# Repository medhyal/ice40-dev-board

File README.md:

# ice40-dev-board

ICE40 FPGA Development Board

- ICE40UP5K FPGA
- Built in Programmer

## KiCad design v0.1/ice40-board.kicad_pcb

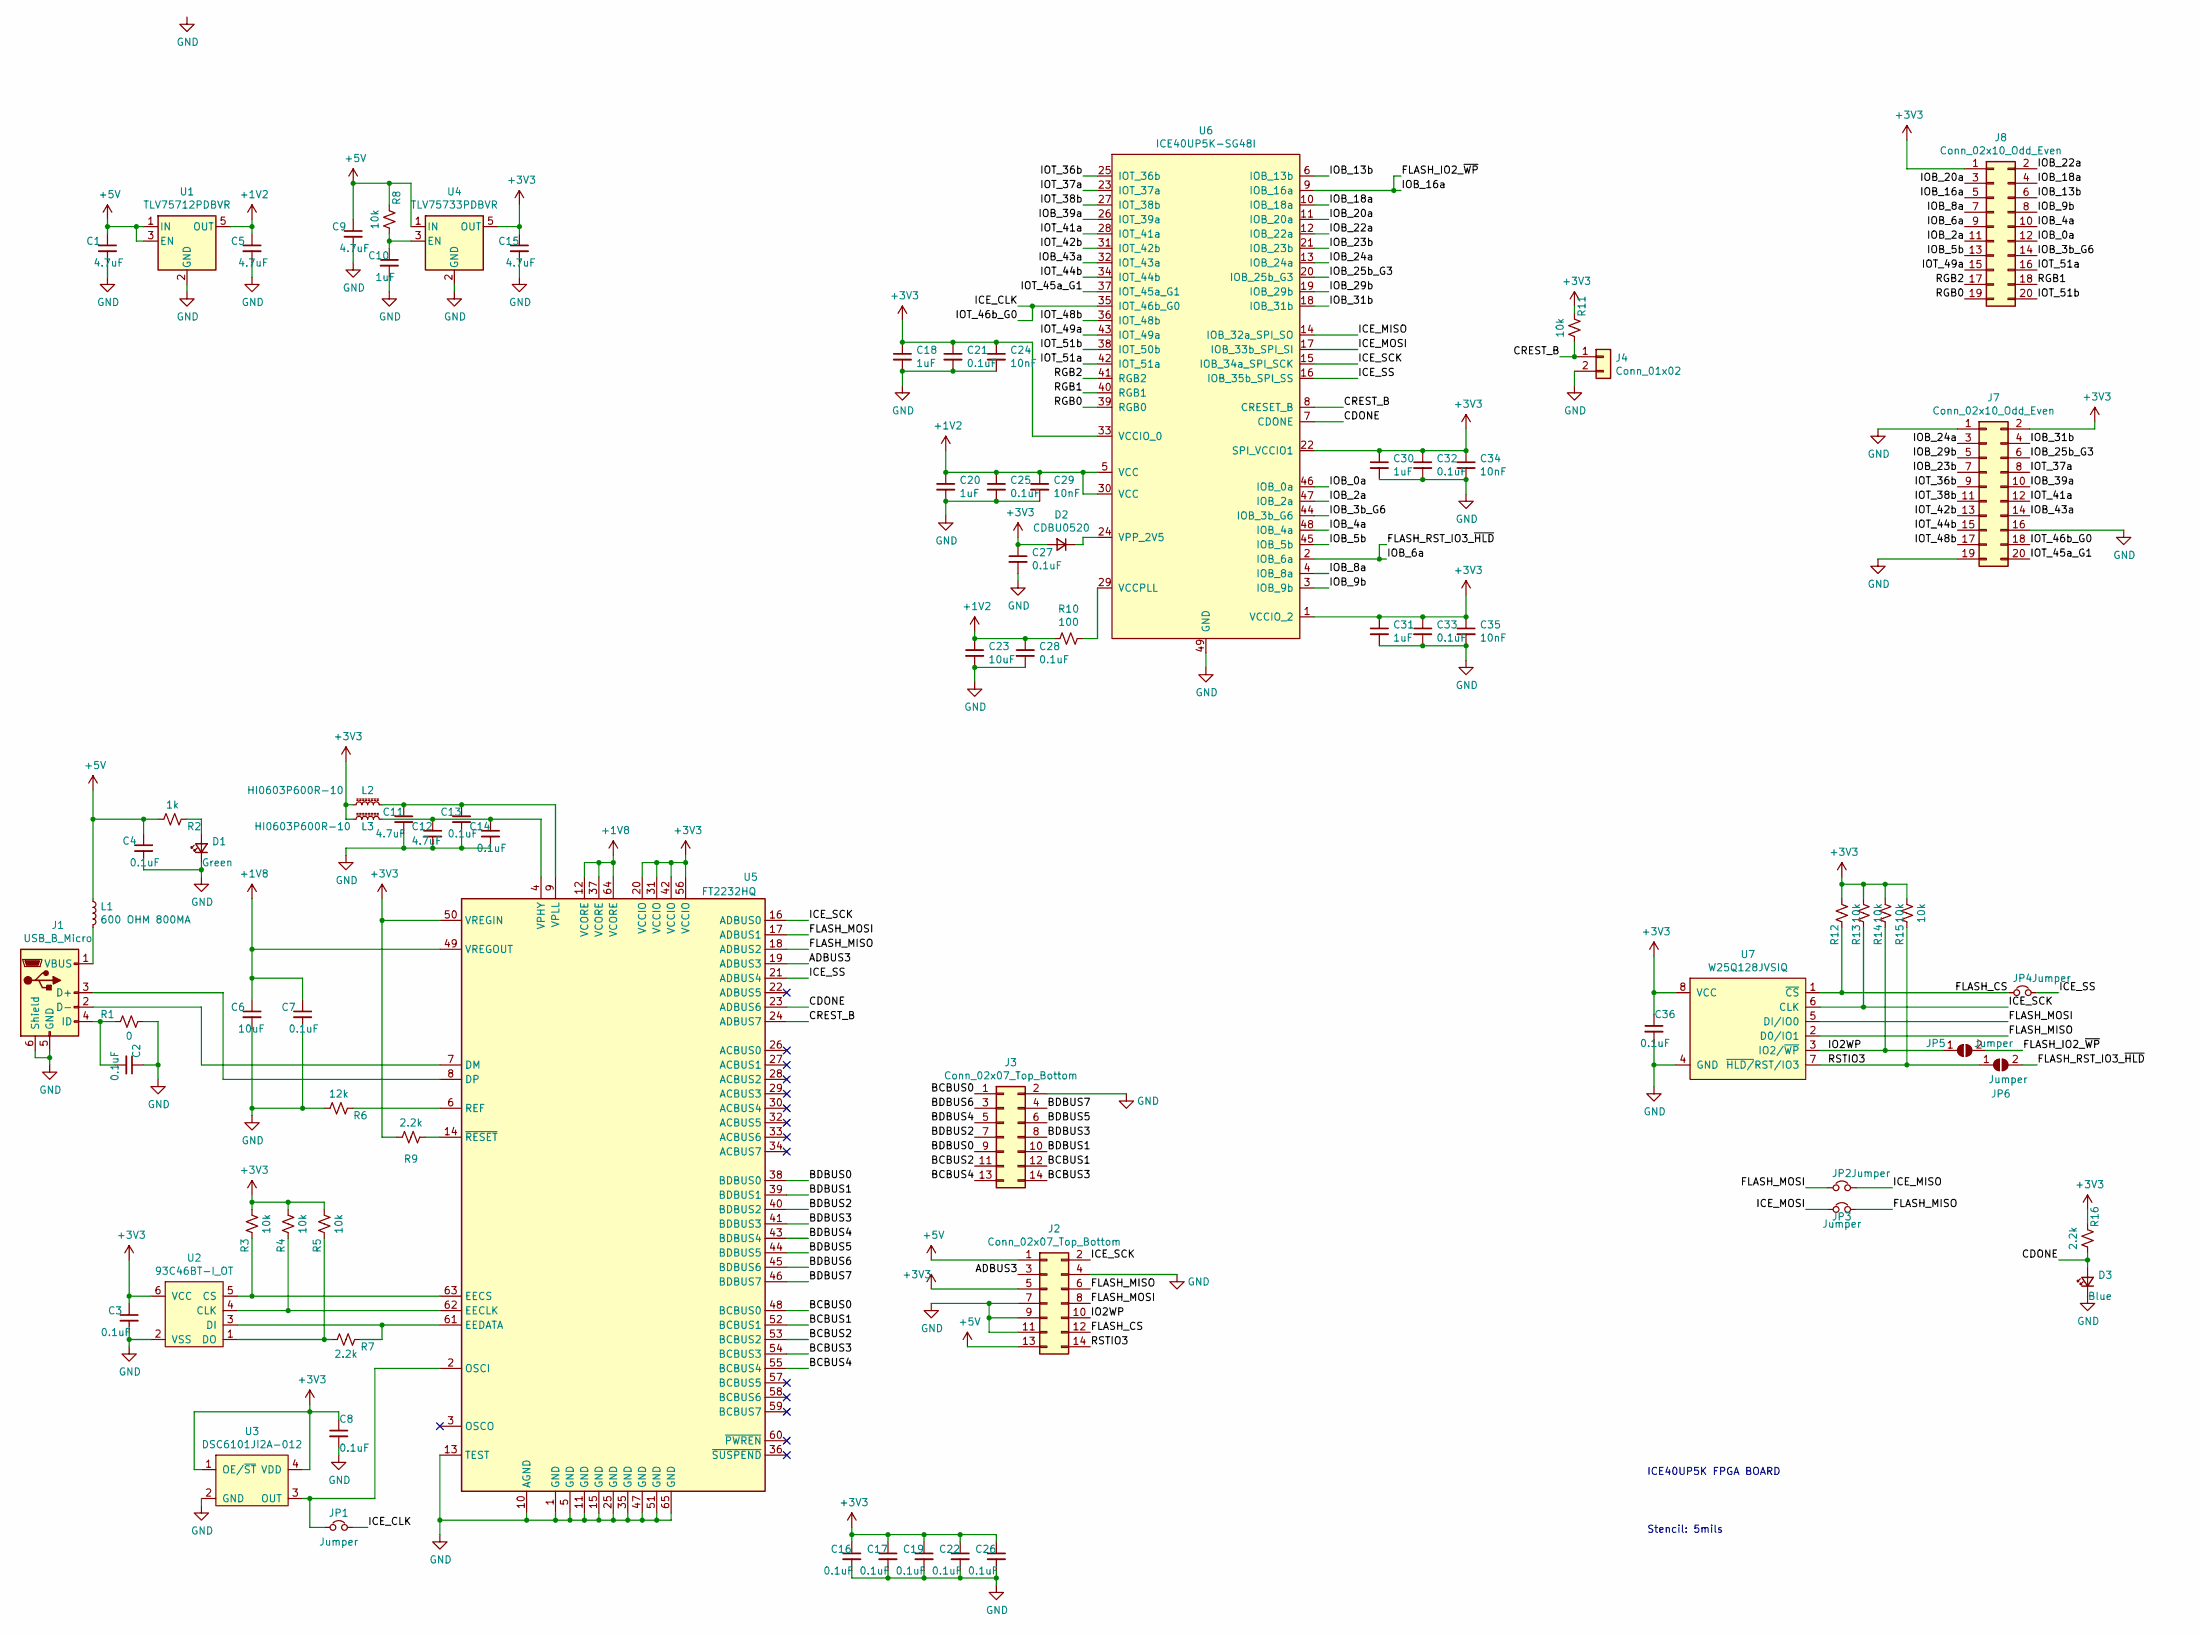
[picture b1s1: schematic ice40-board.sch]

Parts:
C1, C5, C9, C15: 4.7uF; C_0603_1608Metric
C2, C3, C7, C8, C13, C14, C16, C17, C19, C21, C22, C25, C26, C27, C28, C32, C33, C36: 0.1uF; C_0402_1005Metric
C4: 0.1uF; C_0603_1608Metric
C6, C23: 10uF; C_0402_1005Metric
C10, C18, C20, C30, C31: 1uF; C_0402_1005Metric
C11, C12: 4.7uF; C_0402_1005Metric
C24, C29, C34, C35: 10nF; C_0402_1005Metric
D1: Green; LED_0603_1608Metric
D2: CDBU0520; D_0603_1608Metric
D3: Blue; LED_0603_1608Metric
J1: USB_B_Micro; USB_Micro-B_Molex_47346-0001
J2, J3: Conn_02x07_Top_Bottom; PinHeader_2x07_P2.54mm_Vertical
J4: Conn_01x02; PinHeader_1x02_P2.54mm_Vertical
J7, J8: Conn_02x10_Odd_Even; PinHeader_2x10_P2.54mm_Vertical
JP1, JP5, JP6: Jumper; SolderJumper-2_P1.3mm_Open_Pad1.0x1.5mm
JP2, JP3: Jumper; SolderJumper-2_P1.3mm_Bridged_RoundedPad1.0x1.5mm
JP4: Jumper; SolderJumper-2_P1.3mm_Bridged_Pad1.0x1.5mm
L1: 600 OHM 800MA; L_0603_1608Metric
L2, L3: HI0603P600R-10; L_0603_1608Metric
R1: 0; R_0402_1005Metric
R2: 1k; R_0402_1005Metric
R3, R4, R5, R8, R11, R12, R13, R14, R15: 10k; R_0402_1005Metric
R6: 12k; R_0402_1005Metric
R7, R9, R16: 2.2k; R_0402_1005Metric
R10: 100; R_0402_1005Metric
U1: ‎TLV75712PDBVR‎; SOT-23-5
U2: 93C46BT-I_OT; SOT-23-6
U3: DSC6101JI2A-012
U4: ‎TLV75733PDBVR‎; SOT-23-5
U5: FT2232HQ; QFN-64-1EP_9x9mm_P0.5mm_EP4.35x4.35mm
U6: ICE40UP5K-SG48I‎; QFN-48-1EP_7x7mm_P0.5mm_EP5.3x5.3mm
U7: W25Q128JVSIQ; SOIC-8_5.275x5.275mm_P1.27mm

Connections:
+1V2: C5.1, C20.1, C23.1, C25.1, C28.1, C29.1, R10.2, U1.5 (OUT), U6.5 (VCC), U6.30 (VCC)
+1V8: C6.1, C7.1, U5.12 (VCORE), U5.37 (VCORE), U5.49 (VREGOUT), U5.64 (VCORE)
+3V3: C3.1, C8.1, C15.1, C16.1, C17.1, C18.1, C19.1, C21.1, C22.1, C24.1, C26.1, C27.1, C30.1, C31.1, C32.1, C33.1, C34.1, C35.1, C36.1, D2.2 (A), J2.5, J7.2, J8.1, L2.1, L3.1, R3.1, R4.1, R5.1, R9.1, R11.2, R12.1, R13.1, R14.1, R15.1, R16.2, U2.6 (VCC), U3.1 (OE/~ST), U3.4 (VDD), U4.5 (OUT), U5.20 (VCCIO), U5.31 (VCCIO), U5.42 (VCCIO), U5.50 (VREGIN), U5.56 (VCCIO), U6.1 (VCCIO_2), U6.22 (SPI_VCCIO1), U6.33 (VCCIO_0), U7.8 (VCC)
+5V: C1.1, C4.1, C9.1, J2.1, J2.13, L1.1, R2.1, R8.2, U1.1 (IN), U1.3 (EN), U4.1 (IN)
/ADBUS3: J2.3, U5.19 (ADBUS3)
/BCBUS0: J3.1, U5.48 (BCBUS0)
/BCBUS1: J3.12, U5.52 (BCBUS1)
/BCBUS2: J3.11, U5.53 (BCBUS2)
/BCBUS3: J3.14, U5.54 (BCBUS3)
/BCBUS4: J3.13, U5.55 (BCBUS4)
/BDBUS0: J3.9, U5.38 (BDBUS0)
/BDBUS1: J3.10, U5.39 (BDBUS1)
/BDBUS2: J3.7, U5.40 (BDBUS2)
/BDBUS3: J3.8, U5.41 (BDBUS3)
/BDBUS4: J3.5, U5.43 (BDBUS4)
/BDBUS5: J3.6, U5.44 (BDBUS5)
/BDBUS6: J3.3, U5.45 (BDBUS6)
/BDBUS7: J3.4, U5.46 (BDBUS7)
/CDONE: D3.2 (A), R16.1, U5.23 (ADBUS6), U6.7 (CDONE)
/CREST_B: J4.1, R11.1, U5.24 (ADBUS7), U6.8 (CRESET_B)
/FLASH_CS: J2.12, JP4.1, R12.2, U7.1 (~CS)
/FLASH_IO2_~WP: J8.5, JP5.2 (B), U6.9 (IOB_16a)
/FLASH_MISO: J2.6, JP3.2, U5.18 (ADBUS2), U7.2 (D0/IO1)
/FLASH_MOSI: J2.8, JP2.1, U5.17 (ADBUS1), U7.5 (DI/IO0)
/FLASH_RST_IO3_~HLD: J8.9, JP6.2 (B), U6.2 (IOB_6a)
/ICE_CLK: J7.18, JP1.2, U6.35 (IOT_46b_G0)
/ICE_MISO: JP2.2, U6.14 (IOB_32a_SPI_SO)
/ICE_MOSI: JP3.1, U6.17 (IOB_33b_SPI_SI)
/ICE_SCK: J2.2, R13.2, U5.16 (ADBUS0), U6.15 (IOB_34a_SPI_SCK), U7.6 (CLK)
/ICE_SS: JP4.2, U5.21 (ADBUS4), U6.16 (IOB_35b_SPI_SS)
/IO2WP: J2.10, JP5.1 (A), R14.2, U7.3 (IO2/~WP)
/IOB_0a: J8.12, U6.46 (IOB_0a)
/IOB_2a: J8.11, U6.47 (IOB_2a)
/IOB_3b_G6: J8.14, U6.44 (IOB_3b_G6)
/IOB_4a: J8.10, U6.48 (IOB_4a)
/IOB_5b: J8.13, U6.45 (IOB_5b)
/IOB_8a: J8.7, U6.4 (IOB_8a)
/IOB_9b: J8.8, U6.3 (IOB_9b)
/IOB_13b: J8.6, U6.6 (IOB_13b)
/IOB_18a: J8.4, U6.10 (IOB_18a)
/IOB_20a: J8.3, U6.11 (IOB_20a)
/IOB_22a: J8.2, U6.12 (IOB_22a)
/IOB_23b: J7.7, U6.21 (IOB_23b)
/IOB_24a: J7.3, U6.13 (IOB_24a)
/IOB_25b_G3: J7.6, U6.20 (IOB_25b_G3)
/IOB_29b: J7.5, U6.19 (IOB_29b)
/IOB_31b: J7.4, U6.18 (IOB_31b)
/IOB_39a: J7.10, U6.26 (IOT_39a)
/IOB_43a: J7.14, U6.32 (IOT_43a)
/IOT_36b: J7.9, U6.25 (IOT_36b)
/IOT_37a: J7.8, U6.23 (IOT_37a)
/IOT_38b: J7.11, U6.27 (IOT_38b)
/IOT_41a: J7.12, U6.28 (IOT_41a)
/IOT_42b: J7.13, U6.31 (IOT_42b)
/IOT_44b: J7.15, U6.34 (IOT_44b)
/IOT_45a_G1: J7.20, U6.37 (IOT_45a_G1)
/IOT_48b: J7.17, U6.36 (IOT_48b)
/IOT_49a: J8.15, U6.43 (IOT_49a)
/IOT_51a: J8.16, U6.42 (IOT_51a)
/IOT_51b: J8.20, U6.38 (IOT_50b)
/RGB0: J8.19, U6.39 (RGB0)
/RGB1: J8.18, U6.40 (RGB1)
/RGB2: J8.17, U6.41 (RGB2)
/RSTIO3: J2.14, JP6.1 (A), R15.2, U7.7 (~HLD/~RST/IO3)
GND: C1.2, C2.1, C3.2, C4.2, C5.2, C6.2, C7.2, C8.2, C9.2, C10.2, C11.2, C12.2, C13.2, C14.2, C15.2, C16.2, C17.2, C18.2, C19.2, C20.2, C21.2, C22.2, C23.2, C24.2, C25.2, C26.2, C27.2, C28.2, C29.2, C30.2, C31.2, C32.2, C33.2, C34.2, C35.2, C36.2, D1.1 (K), D3.1 (K), J1.5 (GND), J1.6 (Shield), J2.4, J2.7, J2.9, J2.11, J3.2, J4.2, J7.1, J7.16, J7.19, R1.1, R6.1, U1.2 (GND), U2.2 (VSS), U3.2 (GND), U4.2 (GND), U5.1 (GND), U5.5 (GND), U5.10 (AGND), U5.11 (GND), U5.13 (TEST), U5.15 (GND), U5.25 (GND), U5.35 (GND), U5.47 (GND), U5.51 (GND), U5.65 (GND), U6.49 (GND), U7.4 (GND)
unnamed: C2.2, J1.4 (ID), R1.2
unnamed: C10.1, R8.1, U4.3 (EN)
unnamed: C11.1, C13.1, L2.2, U5.9 (VPLL)
unnamed: C12.1, C14.1, L3.2, U5.4 (VPHY)
unnamed: D1.2 (A), R2.2
unnamed: D2.1 (K), U6.24 (VPP_2V5)
unnamed: J1.1 (VBUS), L1.2
unnamed: J1.2 (D-), U5.7 (DM)
unnamed: J1.3 (D+), U5.8 (DP)
unnamed: JP1.1, U3.3 (OUT), U5.2 (OSCI)
unnamed: R3.2, U2.5 (CS), U5.63 (EECS)
unnamed: R4.2, U2.4 (CLK), U5.62 (EECLK)
unnamed: R5.2, R7.1, U2.1 (DO)
unnamed: R6.2, U5.6 (REF)
unnamed: R7.2, U2.3 (DI), U5.61 (EEDATA)
unnamed: R9.2, U5.14 (~RESET)
unnamed: R10.1, U6.29 (VCCPLL)

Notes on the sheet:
ICE40UP5K FPGA BOARD
Stencil: 5mils

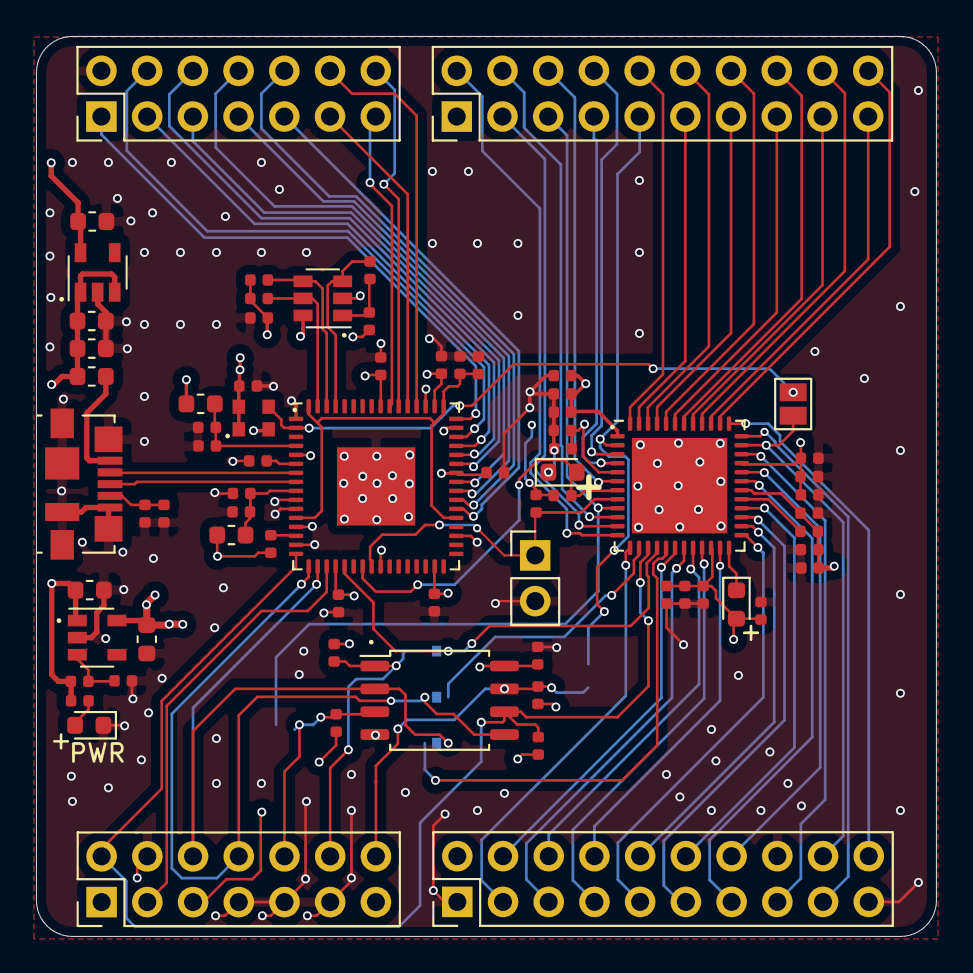
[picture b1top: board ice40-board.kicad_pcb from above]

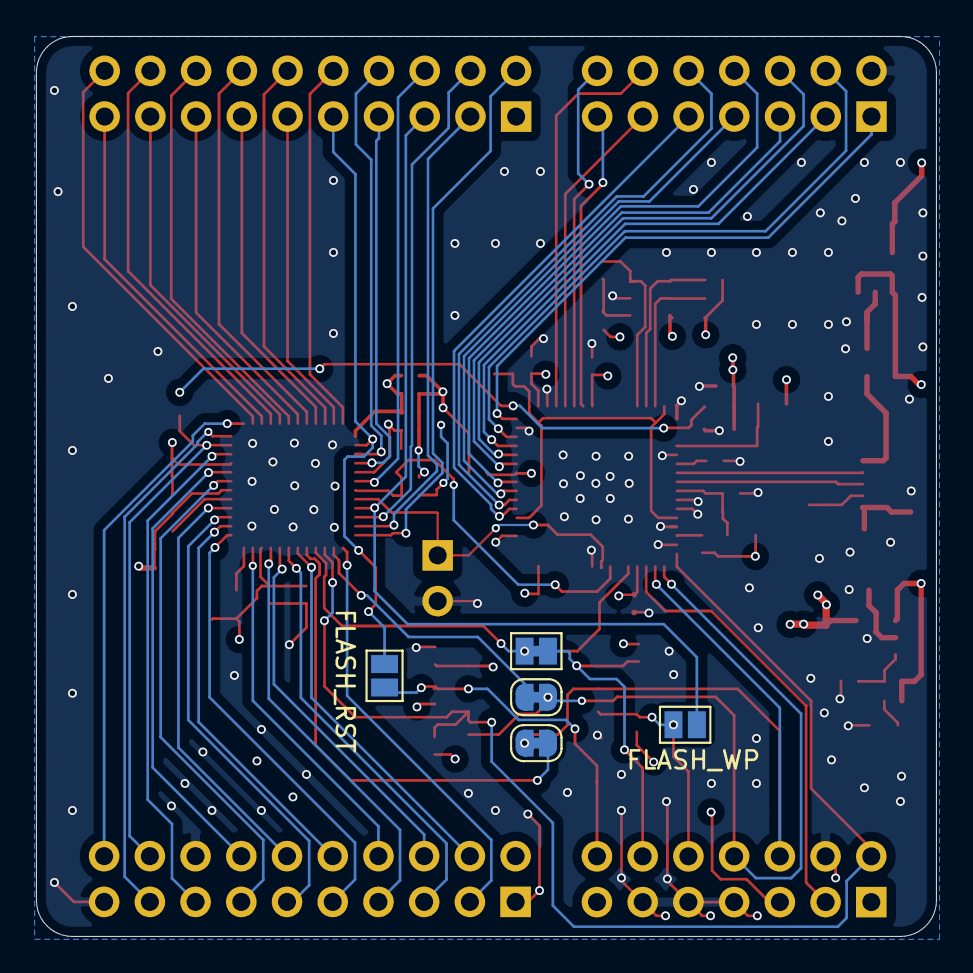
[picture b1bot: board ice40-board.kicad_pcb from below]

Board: 4 copper layers, 50.0 x 50.0 mm, 77 parts (5 on the bottom side), 82 nets.

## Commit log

2021-04-19 Initial Commits
